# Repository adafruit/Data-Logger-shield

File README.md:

Adafruit Data Logger Shield PCB
===============================

PCB files for Adafruit's Data Logger Shield for Arduino

For more details, check out the product page at

-----> https://www.adafruit.com/product/1141

Adafruit invests time and resources providing this open source design, 
please support Adafruit and open-source hardware by purchasing 
products from Adafruit!

Designed by Adafruit Industries.  
Creative Commons Attribution, Share-Alike license, check license.txt for more information
All text above must be included in any redistribution

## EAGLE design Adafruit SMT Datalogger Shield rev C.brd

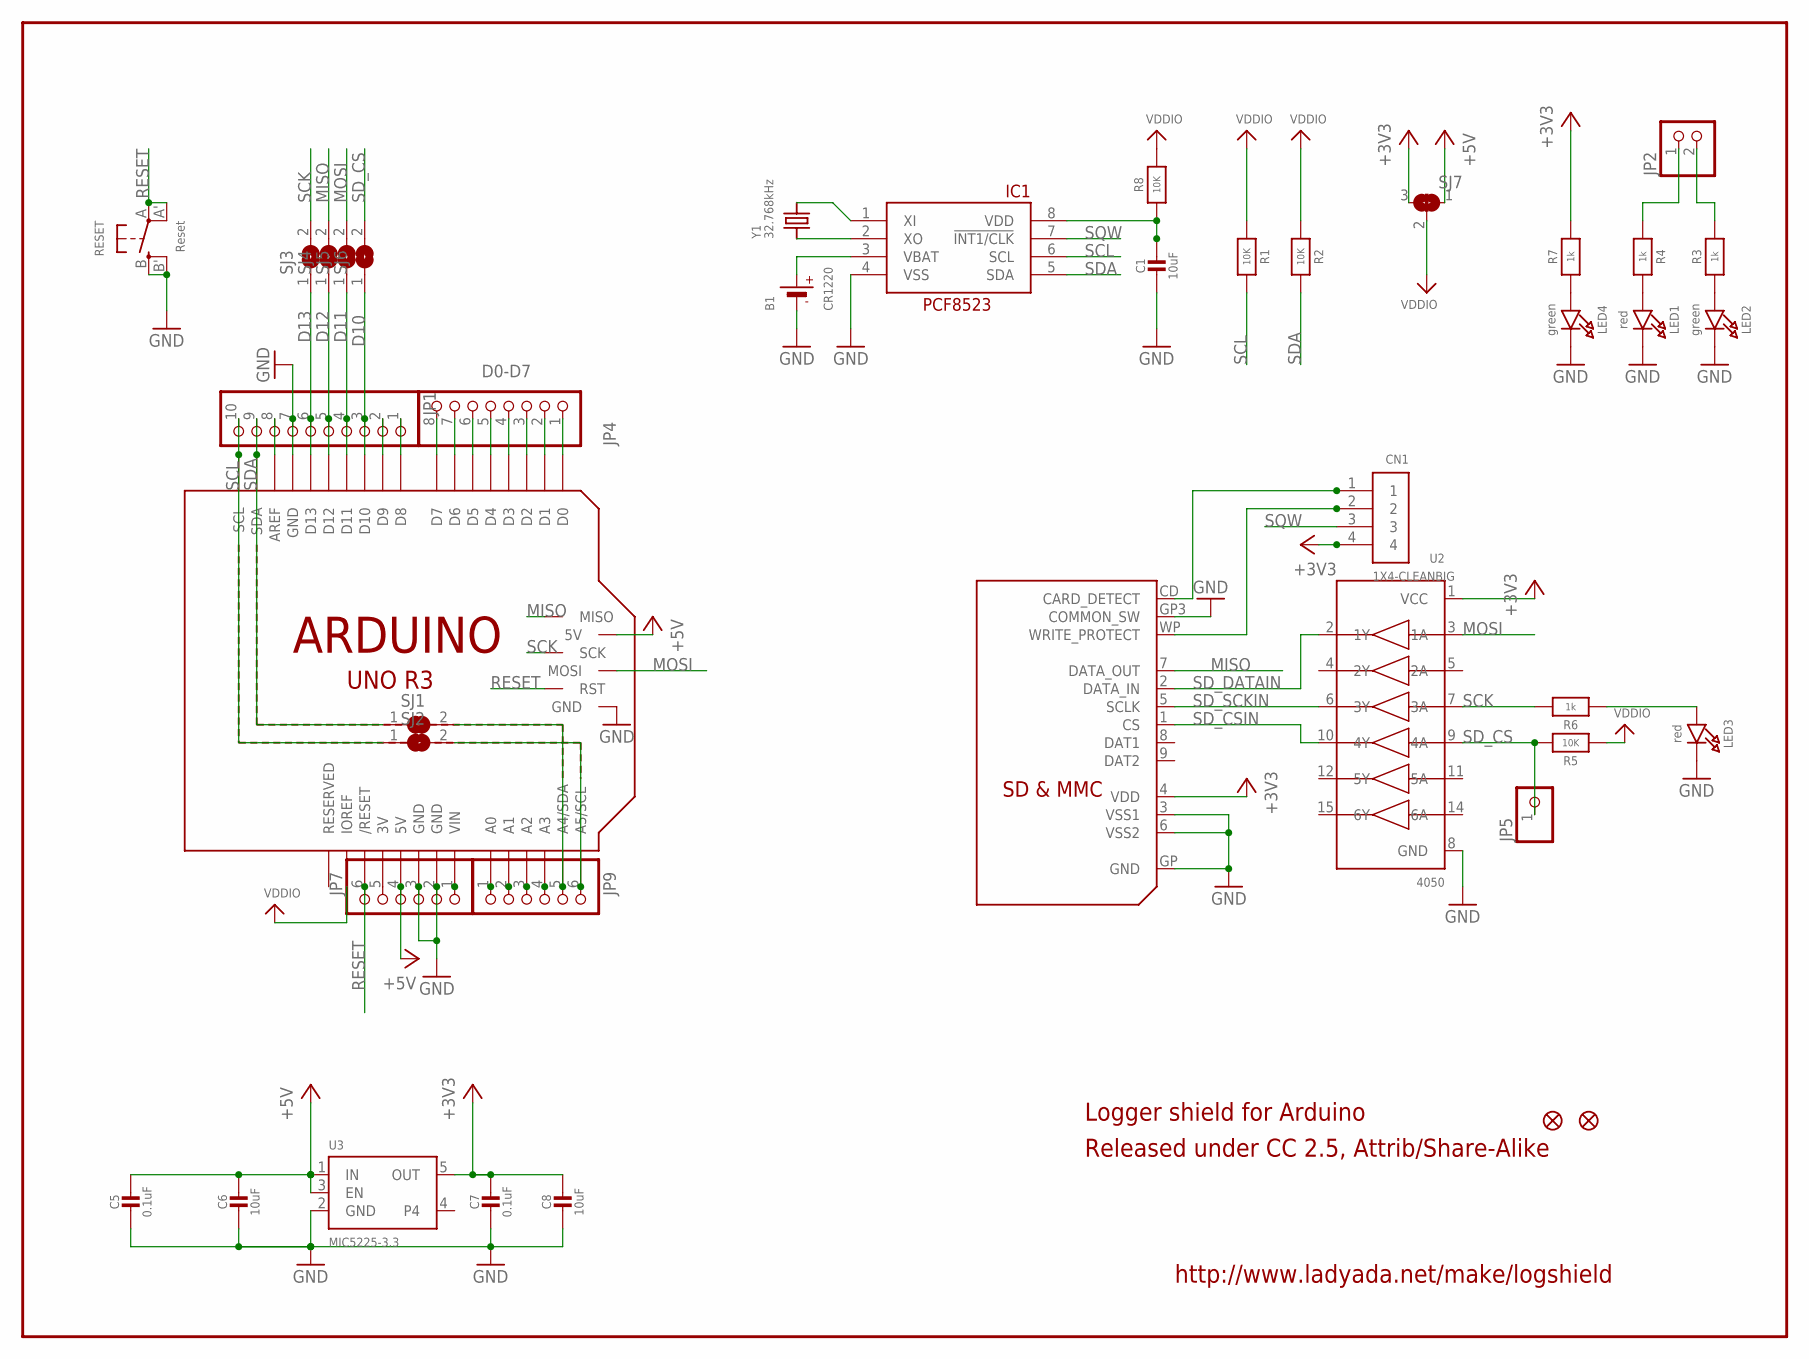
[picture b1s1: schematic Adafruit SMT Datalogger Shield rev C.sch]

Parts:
B1: CR1220
C1, C6, C8: 10uF; 0805-NO
C5, C7: 0.1uF; 0805-NO
CN1: 1X4-CLEANBIG; 1X04-CLEANBIG
FID1, FID3: FIDUCIAL_1MM
IC1: PCF8523T; SOIC8_150MIL
JP1: HEADER-1X1070MIL; 1X10_ROUND70
JP2: HEADER-1X2ROUND; 1X02_ROUND
JP4: D0-D7; 1X08-BIG
JP5: HEADER-1X1ROUND; 1X01_ROUND
JP7, JP9: PINHD-1X6B; 1X06-BIG
LED1, LED3: red; CHIPLED_0805_NOOUTLINE
LED2, LED4: green; CHIPLED_0805_NOOUTLINE
M1: ARDUINO_R3_ICSP_NODIM; ARDUINOR3_ICSP_NODIM
R1, R2, R5, R8: 10K; 0805-NO
R3, R4, R6, R7: 1k; 0805-NO
RESET: Reset; EVQ-Q2_SMALLER
SJ1, SJ2, SJ3, SJ4, SJ5: SOLDERJUMPER; SOLDERJUMPER_ARROW_NOPASTE
SJ6: SOLDERJUMPERCLOSED; SOLDERJUMPER_CLOSEDWIRE
SJ7: SOLDERJUMPER_2WAY; SOLDERJUMPER_2WAY_OPEN_NOPASTE
U2: 4050; SOIC16
U3: MIC5225-3.3; SOT23-5
U$2: SDMMC06132; 06132
Y1: 32.768kHz; CRYSTAL_8X3.8

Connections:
3.3V: JP7.5, M1.3V
+3V3: C7.1, C8.1, CN1.4, R7.2, SJ7.3, U2.1 (VCC), U3.5 (OUT), U$2.4 (VDD)
+5V: C5.1, C6.1, JP7.4, M1.5V, M1.5V_ICSP (5V), SJ7.1, U3.1 (IN), U3.3 (EN)
A4: JP9.5, M1.A4 (A4/SDA), SJ1.2
A5: JP9.6, M1.A5 (A5/SCL), SJ2.2
D10: JP1.3, M1.D10, SJ6.1
D11: JP1.4, M1.D11, SJ5.1
D12: JP1.5, M1.D12, SJ4.1
D13: JP1.6, M1.D13, SJ3.1
GND: B1.-, C1.2, C5.2, C6.2, C7.2, C8.2, IC1.4 (VSS), JP1.7, JP7.2, JP7.3, LED1.C, LED2.C, LED3.C, LED4.C, M1.GND, M1.GND@1 (GND), M1.GND@2 (GND), M1.GND@3 (GND), RESET.B (S), RESET.B' (S1), U2.8 (GND), U3.2 (GND), U$2.3 (VSS1), U$2.6 (VSS2), U$2.GP (GND), U$2.GP3 (COMMON_SW)
MISO: M1.MISO, SJ4.2, U$2.7 (DATA_OUT)
MOSI: M1.MOSI, SJ5.2, U2.3 (1A)
unnamed: LED1.A, R4.2
unnamed: IC1.2 (XO), Y1.P$1 (1)
unnamed: IC1.1 (XI), Y1.P$4 (2)
unnamed: LED2.A, R3.1
unnamed: LED3.A, R6.1
unnamed: C1.1, IC1.8 (VDD), R8.1
unnamed: JP7.1, M1.VIN
unnamed: JP2.2, R3.2
unnamed: JP2.1, R4.1
unnamed: JP4.1, M1.D0
unnamed: JP4.2, M1.D1
unnamed: JP4.3, M1.D2
unnamed: JP4.4, M1.D3
unnamed: JP4.5, M1.D4
unnamed: JP4.6, M1.D5
unnamed: JP4.7, M1.D6
unnamed: JP4.8, M1.D7
unnamed: JP1.8, M1.AREF
unnamed: JP1.2, M1.D9
unnamed: JP1.1, M1.D8
unnamed: LED4.A, R7.1
unnamed: JP9.1, M1.A0
unnamed: JP9.2, M1.A1
unnamed: JP9.3, M1.A2
unnamed: JP9.4, M1.A3
RESET: JP7.6, M1.RESET (/RESET), M1.RESET_ICSP (RST), RESET.A, RESET.A' (P1)
SCK: M1.SCK, R6.2, SJ3.2, U2.7 (3A)
SCL: IC1.6 (SCL), JP1.10, M1.SCL, R1.2, SJ2.1
SDA: IC1.5 (SDA), JP1.9, M1.SDA, R2.2, SJ1.1
SD_CD: CN1.1, U$2.CD (CARD_DETECT)
SD_CS: JP5.1, R5.2, SJ6.2, U2.9 (4A)
SD_CSIN: U2.10 (4Y), U$2.1 (CS)
SD_DATAIN: U2.2 (1Y), U$2.2 (DATA_IN)
SD_SCKIN: U2.6 (3Y), U$2.5 (SCLK)
SD_WP: CN1.2, U$2.WP (WRITE_PROTECT)
SQW: CN1.3, IC1.7 (!INT1/CLK)
VBAT: B1.+$1 (+), B1.+$2 (+), IC1.3 (VBAT)
VDDIO: M1.IOREF, R1.1, R2.1, R5.1, R8.2, SJ7.2

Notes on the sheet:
http://www.ladyada.net/make/logshield
Released under CC 2.5, Attrib/Share-Alike
Logger shield for Arduino

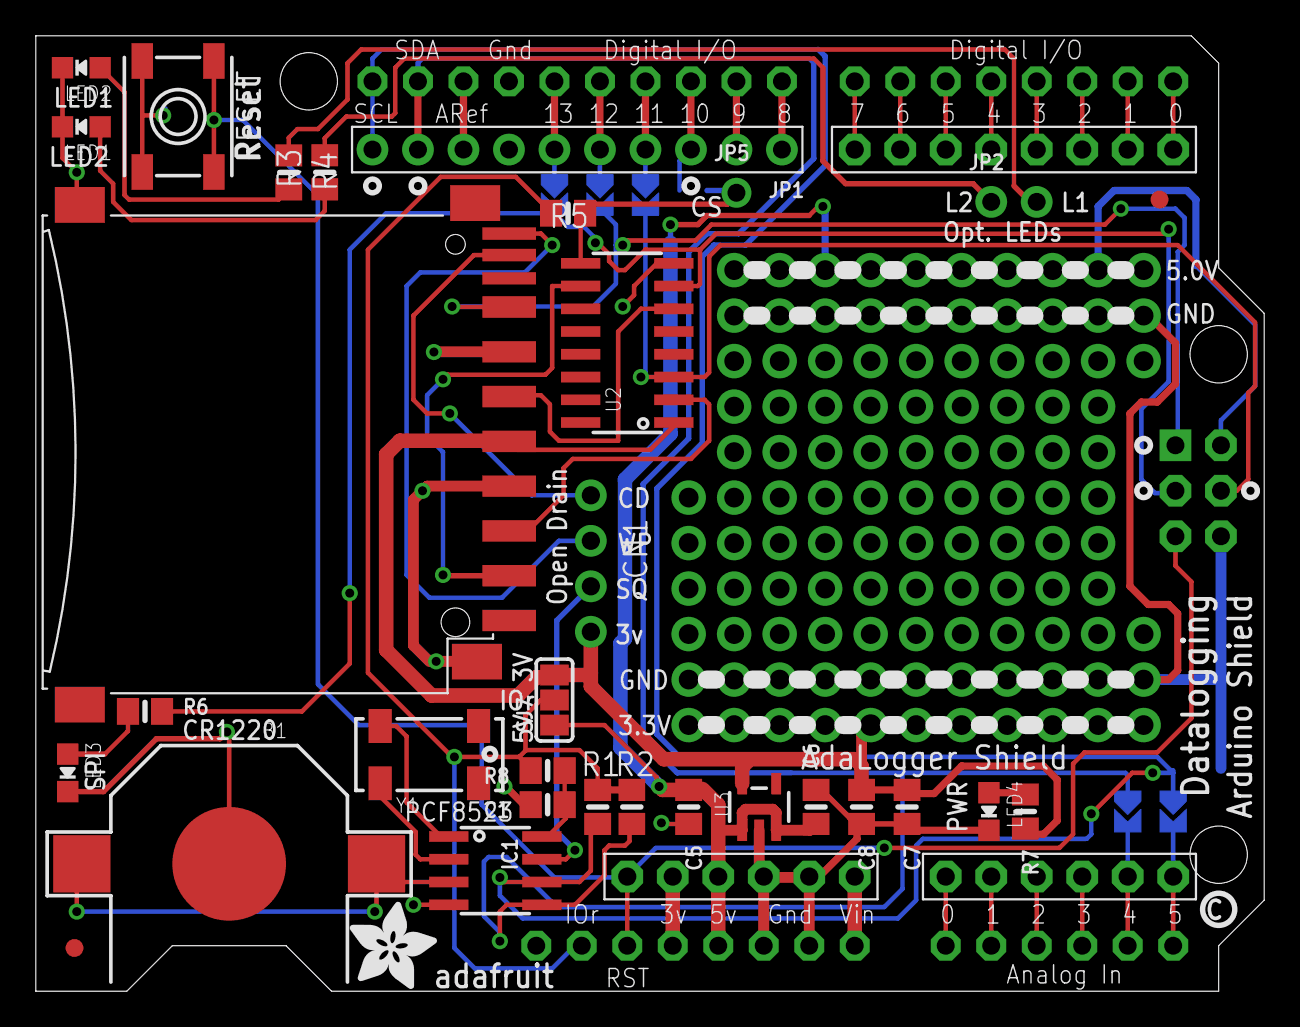
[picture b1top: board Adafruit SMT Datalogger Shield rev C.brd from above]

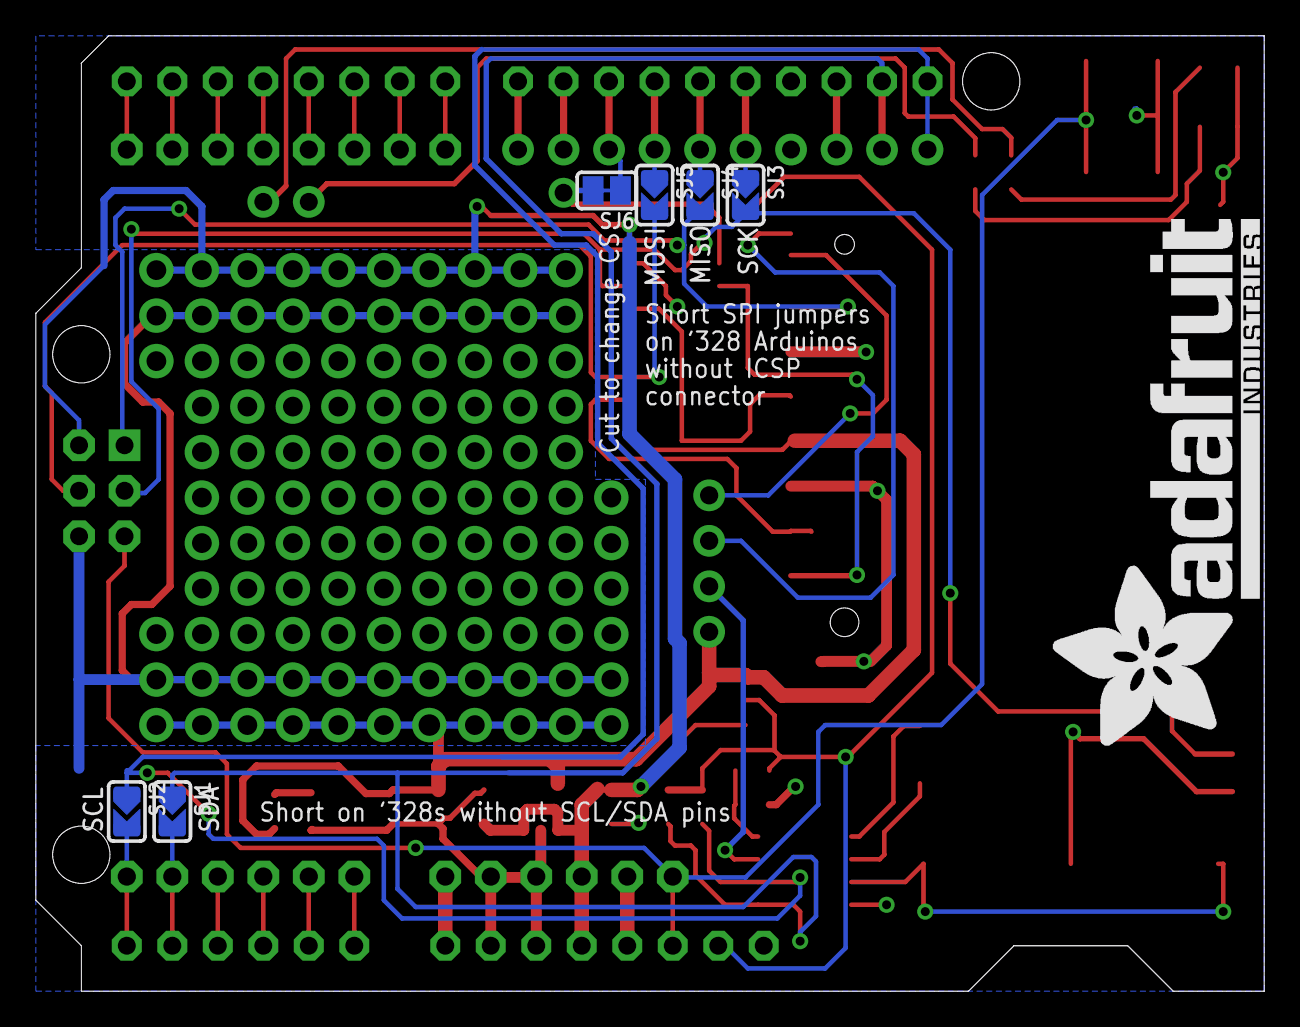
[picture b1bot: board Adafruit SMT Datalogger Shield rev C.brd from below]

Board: 2 copper layers, 68.6 x 53.3 mm, 44 parts (7 on the bottom side), 50 nets.

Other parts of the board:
U$1: ADAFRUIT_TEXT_30MM
U$3: PCBFEAT-REV-040
U$5: ADAFRUIT_5MM

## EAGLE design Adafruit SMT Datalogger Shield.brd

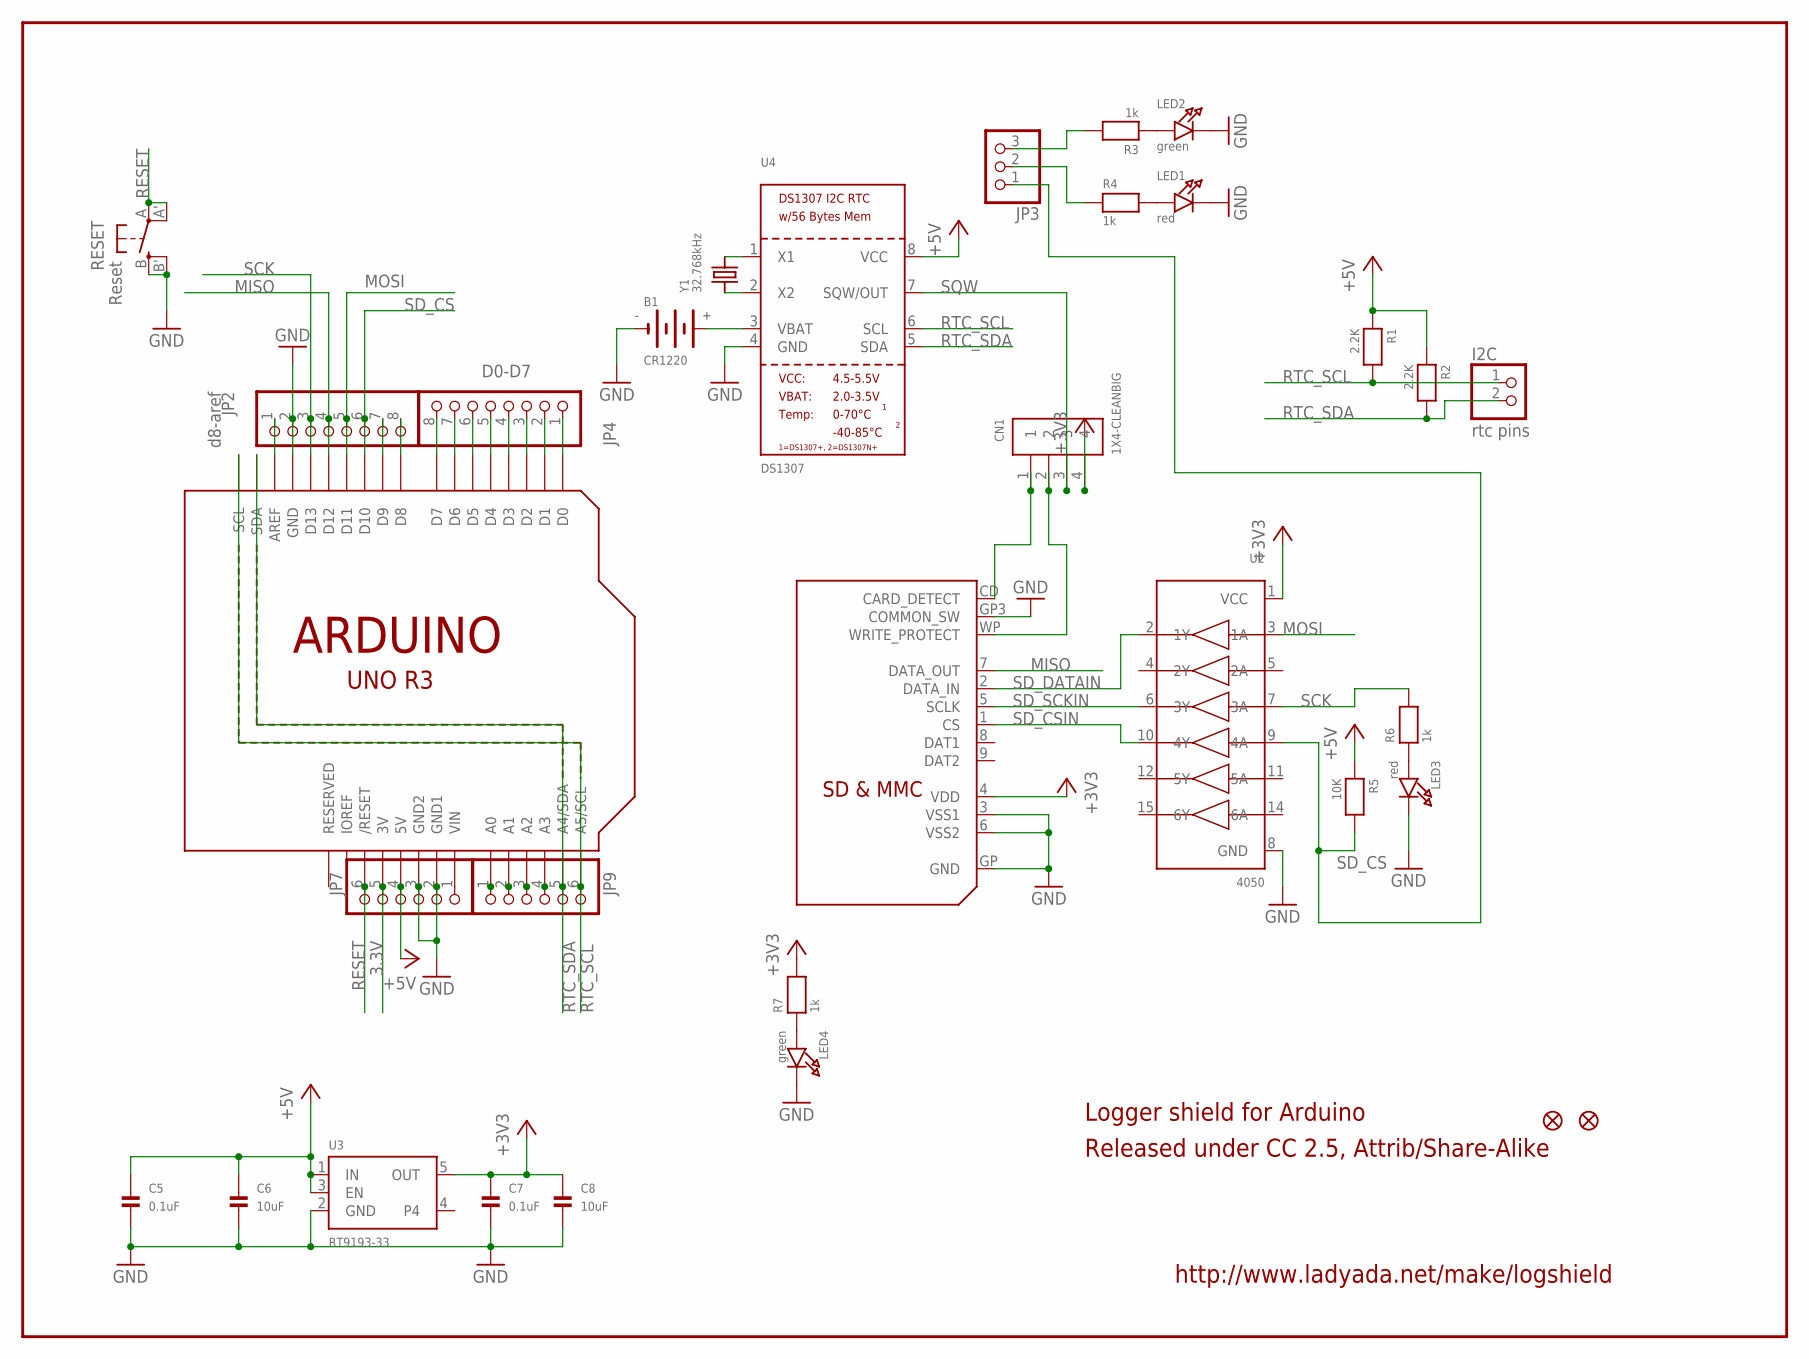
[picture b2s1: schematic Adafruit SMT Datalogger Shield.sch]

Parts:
B1: CR1220
C5, C7: 0.1uF; 0805
C6, C8: 10uF; 0805
CN1: 1X4-CLEANBIG; 1X04-CLEANBIG
FID1, FID3: FIDUCIAL1X2.5; FIDUCIAL-1X2.5
I2C: rtc pins; 1X02
JP2: d8-aref; 1X08-BIG
JP3: HEADER-1X3ROUND; 1X03_ROUND
JP4: D0-D7; 1X08-BIG
JP7, JP9: PINHD-1X6B; 1X06-BIG
LED1, LED3: red; CHIPLED_0805
LED2, LED4: green; CHIPLED_0805
R1, R2: 2.2K; 0805
R3, R4, R6, R7: 1k; 0805
R5: 10K; 0805
RESET: Reset; EVQ-Q2
U1: ARDUINOR3-DIMENSION; ARDUINOR3
U2: 4050; SOIC16
U3: RT9193-33; SOT23-5
U4: DS1307; SOIC8_150MIL
U$2: SDMMC06132; 06132
Y1: 32.768kHz; CRYSTAL_8X3.8

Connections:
3.3V: JP7.5, U1.3V
+3V3: C7.1, C8.1, CN1.4, R7.2, U2.1 (VCC), U3.5 (OUT), U$2.4 (VDD)
+5V: C5.1, C6.1, JP7.4, R1.1, R2.1, R5.1, U1.5V, U3.1 (IN), U3.3 (EN), U4.8 (VCC)
GND: B1.-, C5.2, C6.2, C7.2, C8.2, JP2.2, JP7.2, JP7.3, LED1.C, LED2.C, LED3.C, LED4.C, RESET.B (S), RESET.B' (S1), U1.GND, U1.GND1, U1.GND2, U2.8 (GND), U3.2 (GND), U4.4 (GND), U$2.3 (VSS1), U$2.6 (VSS2), U$2.GP (GND), U$2.GP3 (COMMON_SW)
MISO: JP2.4, U1.D12, U$2.7 (DATA_OUT)
MOSI: JP2.5, U1.D11, U2.3 (1A)
unnamed: LED1.A, R4.2
unnamed: U4.2 (X2), Y1.P$1 (1)
unnamed: U4.1 (X1), Y1.P$4 (2)
unnamed: LED2.A, R3.1
unnamed: LED3.A, R6.1
unnamed: B1.+$1 (+), U4.3 (VBAT)
unnamed: JP7.1, U1.VIN
unnamed: JP3.3, R3.2
unnamed: JP3.2, R4.1
unnamed: JP4.1, U1.D0
unnamed: JP4.2, U1.D1
unnamed: JP4.3, U1.D2
unnamed: JP4.4, U1.D3
unnamed: JP4.5, U1.D4
unnamed: JP4.6, U1.D5
unnamed: JP4.7, U1.D6
unnamed: JP4.8, U1.D7
unnamed: JP2.1, U1.AREF
unnamed: JP2.7, U1.D9
unnamed: JP2.8, U1.D8
unnamed: LED4.A, R7.1
unnamed: JP9.1, U1.A0
unnamed: JP9.2, U1.A1
unnamed: JP9.3, U1.A2
unnamed: JP9.4, U1.A3
RESET: JP7.6, RESET.A, RESET.A' (P1), U1.RESET (/RESET)
RTC_SCL: I2C.1, JP9.6, R1.2, U1.A5 (A5/SCL), U1.SCL, U4.6 (SCL)
RTC_SDA: I2C.2, JP9.5, R2.2, U1.A4 (A4/SDA), U1.SDA, U4.5 (SDA)
SCK: JP2.3, R6.2, U1.D13, U2.7 (3A)
SD_CD: CN1.1, U$2.CD (CARD_DETECT)
SD_CS: JP2.6, JP3.1, R5.2, U1.D10, U2.9 (4A)
SD_CSIN: U2.10 (4Y), U$2.1 (CS)
SD_DATAIN: U2.2 (1Y), U$2.2 (DATA_IN)
SD_SCKIN: U2.6 (3Y), U$2.5 (SCLK)
SD_WP: CN1.2, U$2.WP (WRITE_PROTECT)
SQW: CN1.3, U4.7 (SQW/OUT)

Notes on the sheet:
http://www.ladyada.net/make/logshield
Released under CC 2.5, Attrib/Share-Alike
Logger shield for Arduino

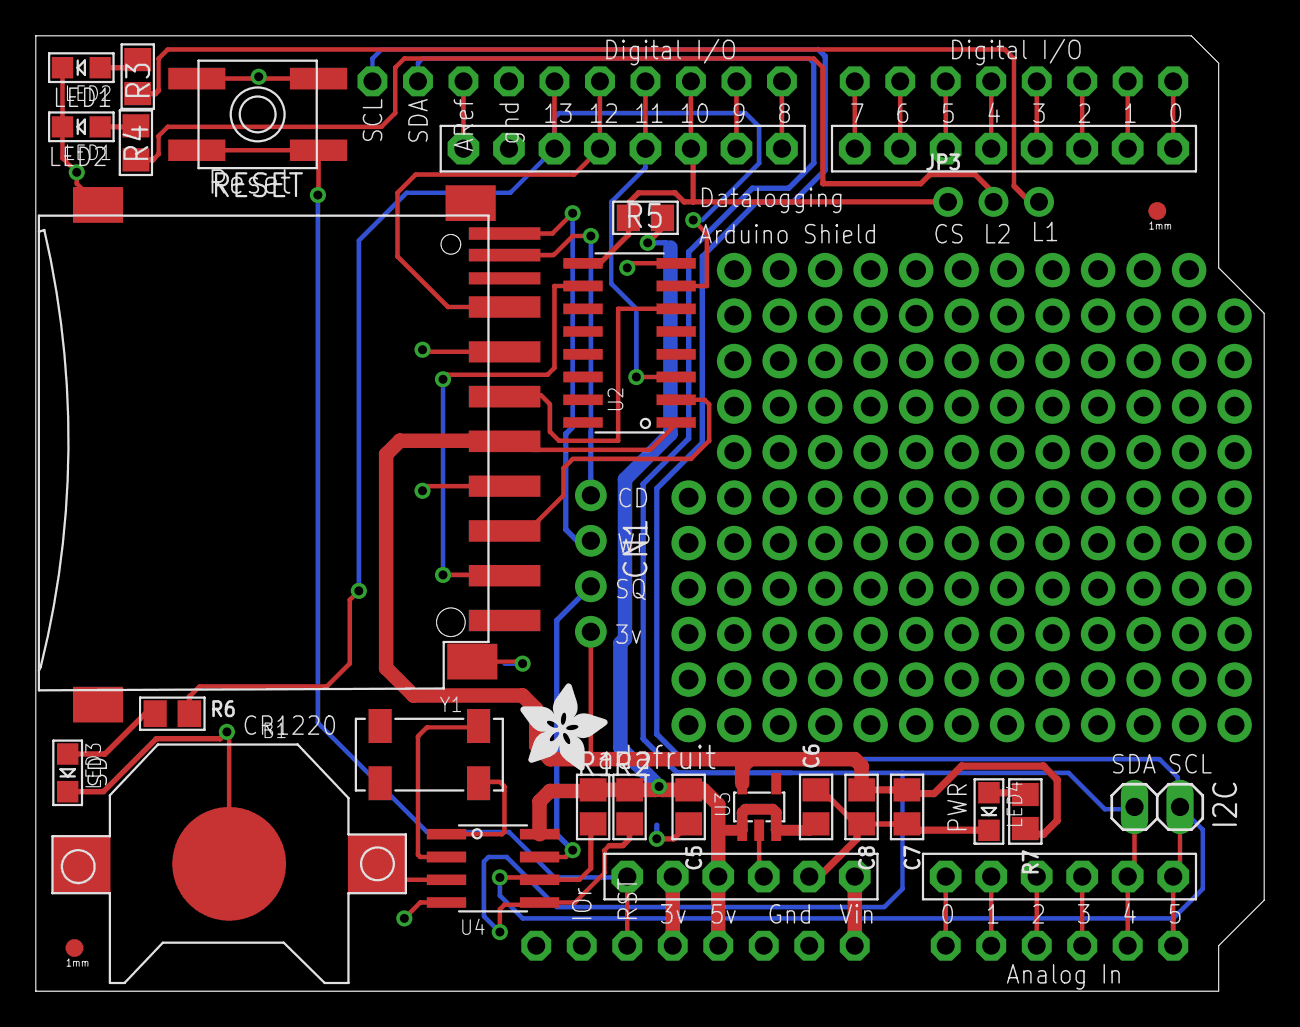
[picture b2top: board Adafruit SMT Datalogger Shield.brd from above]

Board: 2 copper layers, 68.6 x 53.3 mm, 34 parts (1 on the bottom side), 42 nets.

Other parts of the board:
U$1: ADAFRUIT_TEXT_30MM
U$5: ADAFRUIT_5MM

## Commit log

2010-04-13 First commit (of v1)
2010-04-13 updated parts to adafruit library
2015-01-16 updated with the SMT files too!
2015-01-16 added a readme
2018-11-27 rename and add latest!
2018-11-28 fixval
